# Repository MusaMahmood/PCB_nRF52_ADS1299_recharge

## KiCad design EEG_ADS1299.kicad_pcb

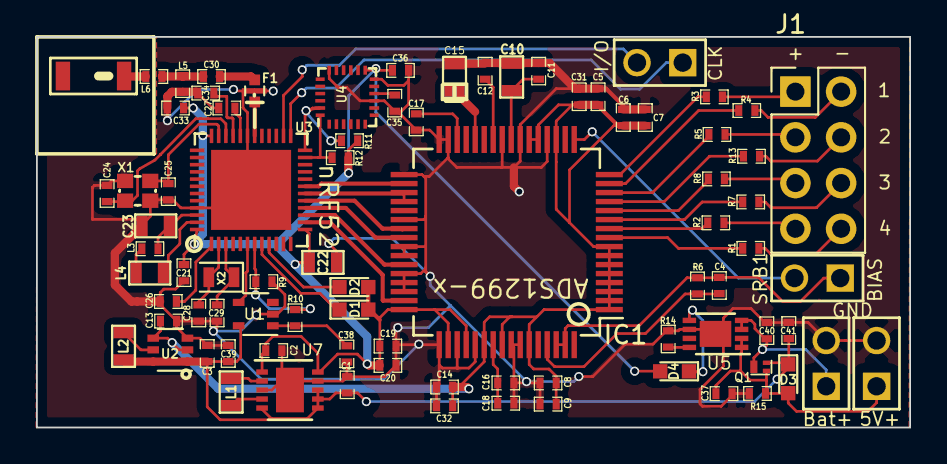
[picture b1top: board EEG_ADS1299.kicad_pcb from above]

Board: 2 copper layers, 48.5 x 21.7 mm, 83 parts (0 on the bottom side), 65 nets.

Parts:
A1: CHIP-ANT; JTI-2450AT18A100-CHIP-ANT
C1, C2, C3, C13, C38, C39: 10uF; SM0402
C4: 1.0nF; SM0402
C5, C6, C8, C12, C14, C16, C17, C19: 1uF; SM0402
C7, C9, C11, C18, C20, C31, C32: 0.1uF; SM0402
C10: 10uF; SM0603
C15: 100µF; SM0603_Tant
C21: 4.7µF; SM0402
C22: 100nF; SM0603
C23: 1.0µF; SM0603
C24, C25, C28, C29: 12pF; SM0402
C26, C33, C35, C36: 100nF; SM0402
C27: N.C.; SM0402
C30: 1.0pF; SM0402
C34: 100pF; SM0402
C37, C40: 4.7uF; SM0402
C41: 1.0uF; SM0402
D1, D2, D4: LED; LED_0603
D3: D_Schottky; LED_0603
F1: 2450FM07A0029; R_0402
IC1: ADS1299; TQFP-64_10x10mm_Pitch0.5mm
J1: Conn_01x08_Male; Pin_Header_Straight_2x04_Pitch2.54mm
J2: Conn_01x02_Male; PIN_ARRAY_2X1
L1: 2.2µH; SM0603
L2: 4.7µH; SM0603
L3: 15nH; SM0402
L4: 10uH; SM0603
L5: 2.7nH; SM0402
L6: 3.9nH; SM0402
P1, P2, P3: CONN_2; PIN_ARRAY_2X1
Q1: DMP21D5UFB4-7B; X2-DFN1006
R1, R2, R3, R4, R5, R7, R8, R13: 30k; SM0402
R6: 1MΩ; SM0402
R9, R10: 1M; SM0402
R11, R12: 10k; SM0402
R14: 2k; SM0402
R15: 100k; SM0402
U1: TPS2294x; SOT-353_SC-70-5
U2: TPS61222; SOT-363_SC-70-6
U3: NRF528XX-QFAA; UQFN-48-1EP_6x6mm_Pitch0.4mm
U4: MPU-9250; QFN-24_3x3mm_Pitch0.4mm
U5: MCP73831; DFN-8-1EP_3x2mm_Pitch0.5mm
U7: TPS63001; DFN-10-1EP_3x3mm_Pitch0.5mm
X1: Crystal_GND24; CRYSTAL-SMD-2.0MMx1.6MM
X2: 32.768 kHz; Crystal_SMD_2012-2pin_2.0x1.2mm

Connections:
5V_in_charge: C37.1, D3.2, P3.1, Q1.1, R15.1, U5.1, U5.2
/AIN_BAT_DIV_VOLTAGE: R9.2, R10.1, U3.7
/BATT_IN: C40.1, P1.1, Q1.2, U5.3, U5.4
/BIAS_ELEC: C4.1, IC1.62, IC1.63, J2.1, R6.1
/DEC1: C26.1, U3.1
/DEC2: C27.1, U3.32
/DEC3: C34.1, U3.33
/DIN: IC1.34, U3.19
/DOUT: IC1.43, U3.15
/LED2: D1.1, U3.8
/LED3: D2.1, U3.9
/LOAD_SW_CTRL: U1.4, U3.6
/RF: C30.1, F1.4
/SCL: R11.2, U3.24, U4.23
/SDI: R12.2, U3.23, U4.24
/SPI_SCLK: IC1.40, U3.16
/SPI_~CS: IC1.39, U3.17
/SRB1: IC1.17, J2.2
/SWDCLK: P2.1, U3.25
/SWDIO: P2.2, U3.26
/VCAP1: C15.1, IC1.28
/VCAP2: C17.1, IC1.30
/VCAP3: C16.1, C18.1, IC1.55
/VCAP4: C12.1, IC1.26
/VREFP: C10.2, C11.2, IC1.24
/Vout: C38.1, R10.2, U1.1
/~DRDY: IC1.47, U3.14
/~PWDN/RESET: IC1.35, IC1.36, U3.18
AVDD: C5.2, C6.2, C7.2, C8.1, C9.1, C13.1, C14.2, C31.2, C32.2, IC1.1, IC1.2, IC1.3, IC1.4, IC1.5, IC1.6, IC1.7, IC1.8, IC1.19, IC1.21, IC1.22, IC1.54, IC1.56, IC1.59, U2.2, U2.4
AVSS: C1.1, C2.2, C3.2, C5.1, C6.1, C7.1, C8.2, C9.2, C10.1, C11.1, C12.2, C13.2, C14.1, C15.2, C16.2, C17.2, C18.2, C19.2, C20.1, C21.1, C22.2, C23.2, C24.1, C25.1, C26.2, C27.2, C28.2, C29.2, C31.1, C32.1, C33.1, C34.2, C35.2, C36.2, C37.2, C38.2, C39.2, C40.2, C41.2, F1.1, F1.3, IC1.20, IC1.23, IC1.25, IC1.31, IC1.32, IC1.33, IC1.38, IC1.41, IC1.42, IC1.44, IC1.45, IC1.46, IC1.49, IC1.51, IC1.53, IC1.57, IC1.58, L5.2, P1.2, P3.2, R9.1, R14.2, R15.2, U1.2, U2.3, U3.31, U3.45, U3.49, U4.9, U4.12, U4.18, U5.6, U5.9, U7.3, U7.9, U7.11, X1.2, X1.4
DVDD: C2.1, C19.1, C20.2, C21.2, C22.1, C33.2, C36.1, D1.2, D2.2, D4.2, IC1.48, IC1.50, IC1.52, R11.1, R12.1, U3.13, U3.36, U3.48, U4.13, U7.1, U7.10
unnamed: A1.1, L6.2
unnamed: C4.2, IC1.61, R6.2
unnamed: C23.1, L3.2, U3.46
unnamed: C24.2, U3.34, X1.1
unnamed: C25.2, U3.35, X1.3
unnamed: C28.1, U3.2, X2.2
unnamed: C29.1, U3.3, X2.1
unnamed: C30.2, L5.1, L6.1
unnamed: C35.1, U4.10
unnamed: D4.1, U5.5
unnamed: F1.2, U3.30
unnamed: IC1.9, R1.1
unnamed: IC1.10, R2.1
unnamed: IC1.11, R7.1
unnamed: IC1.12, R8.1
unnamed: IC1.13, R13.1
unnamed: IC1.14, R5.1
unnamed: IC1.15, R4.1
unnamed: IC1.16, R3.1
unnamed: J1.1, R3.2
unnamed: J1.2, R4.2
unnamed: J1.3, R5.2
unnamed: J1.4, R13.2
unnamed: J1.5, R8.2
unnamed: J1.6, R7.2
unnamed: J1.7, R2.2
unnamed: J1.8, R1.2
unnamed: L1.1, U7.4
unnamed: L1.2, U7.2
unnamed: L2.1, U2.5
unnamed: L3.1, L4.2
unnamed: L4.1, U3.47
unnamed: R14.1, U5.8
VCC: C1.2, C3.1, C39.1, C41.1, D3.1, L2.2, Q1.3, U1.5, U2.1, U2.6, U7.5, U7.6, U7.7, U7.8

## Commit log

2018-09-06 Initial commit
    Cloned from https://github.com/MusaMahmood/KiCAD-EEG-INA828-nRF52
2018-09-10 Removed extraneous components from sch and pcb.
2018-09-10 Remove more extraneous stuff.
2018-09-10 Completed Schematic and updated libraries.
2018-09-10 Finalized schematic with all connectors
2018-09-10 Changed DFN-8 from 2x3mm to 3x2mm
2018-09-10 Added all components, and generated Gerbers.
2018-09-10 Minor edits to finalize.
2018-09-11 Updated R15 value for load sharing circuit.
